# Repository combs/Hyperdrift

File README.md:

Hyperdrift is a panelized LED matrix artwork.

# LED panels
Each panel can have an arbitrary layout of LEDs, as long as they are electrically connected in a 4x16 matrix (4 common cathodes, 16 anodes).

## Mechanical specification

- [Spec PDF](https://github.com/combs/Hyperdrift/raw/refs/heads/main/Mechanical%20specs/Hyperdrift-Mechanical%20spec%20for%20LED%20panels.pdf) 

## Example LED panel layouts

### Grid
This is a straightforward grid of 8x8 pixels.
- [KiCad board and schematic](https://github.com/combs/Hyperdrift/tree/main/LED%20panel%20reference%20design%20-%20Grid)
- [BOM](https://github.com/combs/Hyperdrift/raw/refs/heads/main/LED%20panel%20reference%20design%20-%20Grid/bom/ibom.html) (download and open)
- [Schematic PDF](https://github.com/combs/Hyperdrift/raw/refs/heads/main/LED%20panel%20reference%20design%20-%20Grid/Hyperdrift-Grid.pdf) 
- [Board PDF](https://github.com/combs/Hyperdrift/raw/refs/heads/main/LED%20panel%20reference%20design%20-%20Grid/plots/Hyperdrift-Grid__Assembly.pdf) 

# Display controllers

Each display controller is a 75x100mm board that drives three LED panels (12x16 matrix arrangement). It accepts 12V in. It is designed to allow for either daisy-chained or wagon-wheel bus arrangement.

- [KiCad board and schematic](https://github.com/combs/Hyperdrift/tree/main/Display%20controller)
- [BOM](https://github.com/combs/Hyperdrift/raw/refs/heads/main/Display%20controller/bom/ibom.html) (download and open)
- [Schematic PDF](https://github.com/combs/Hyperdrift/raw/refs/heads/main/Display%20controller/Hyperdrift-Display-Controller.pdf) 
- [Board PDF](https://github.com/combs/Hyperdrift/raw/refs/heads/main/Display%20controller/Hyperdrift-Display-Controller-board.pdf)

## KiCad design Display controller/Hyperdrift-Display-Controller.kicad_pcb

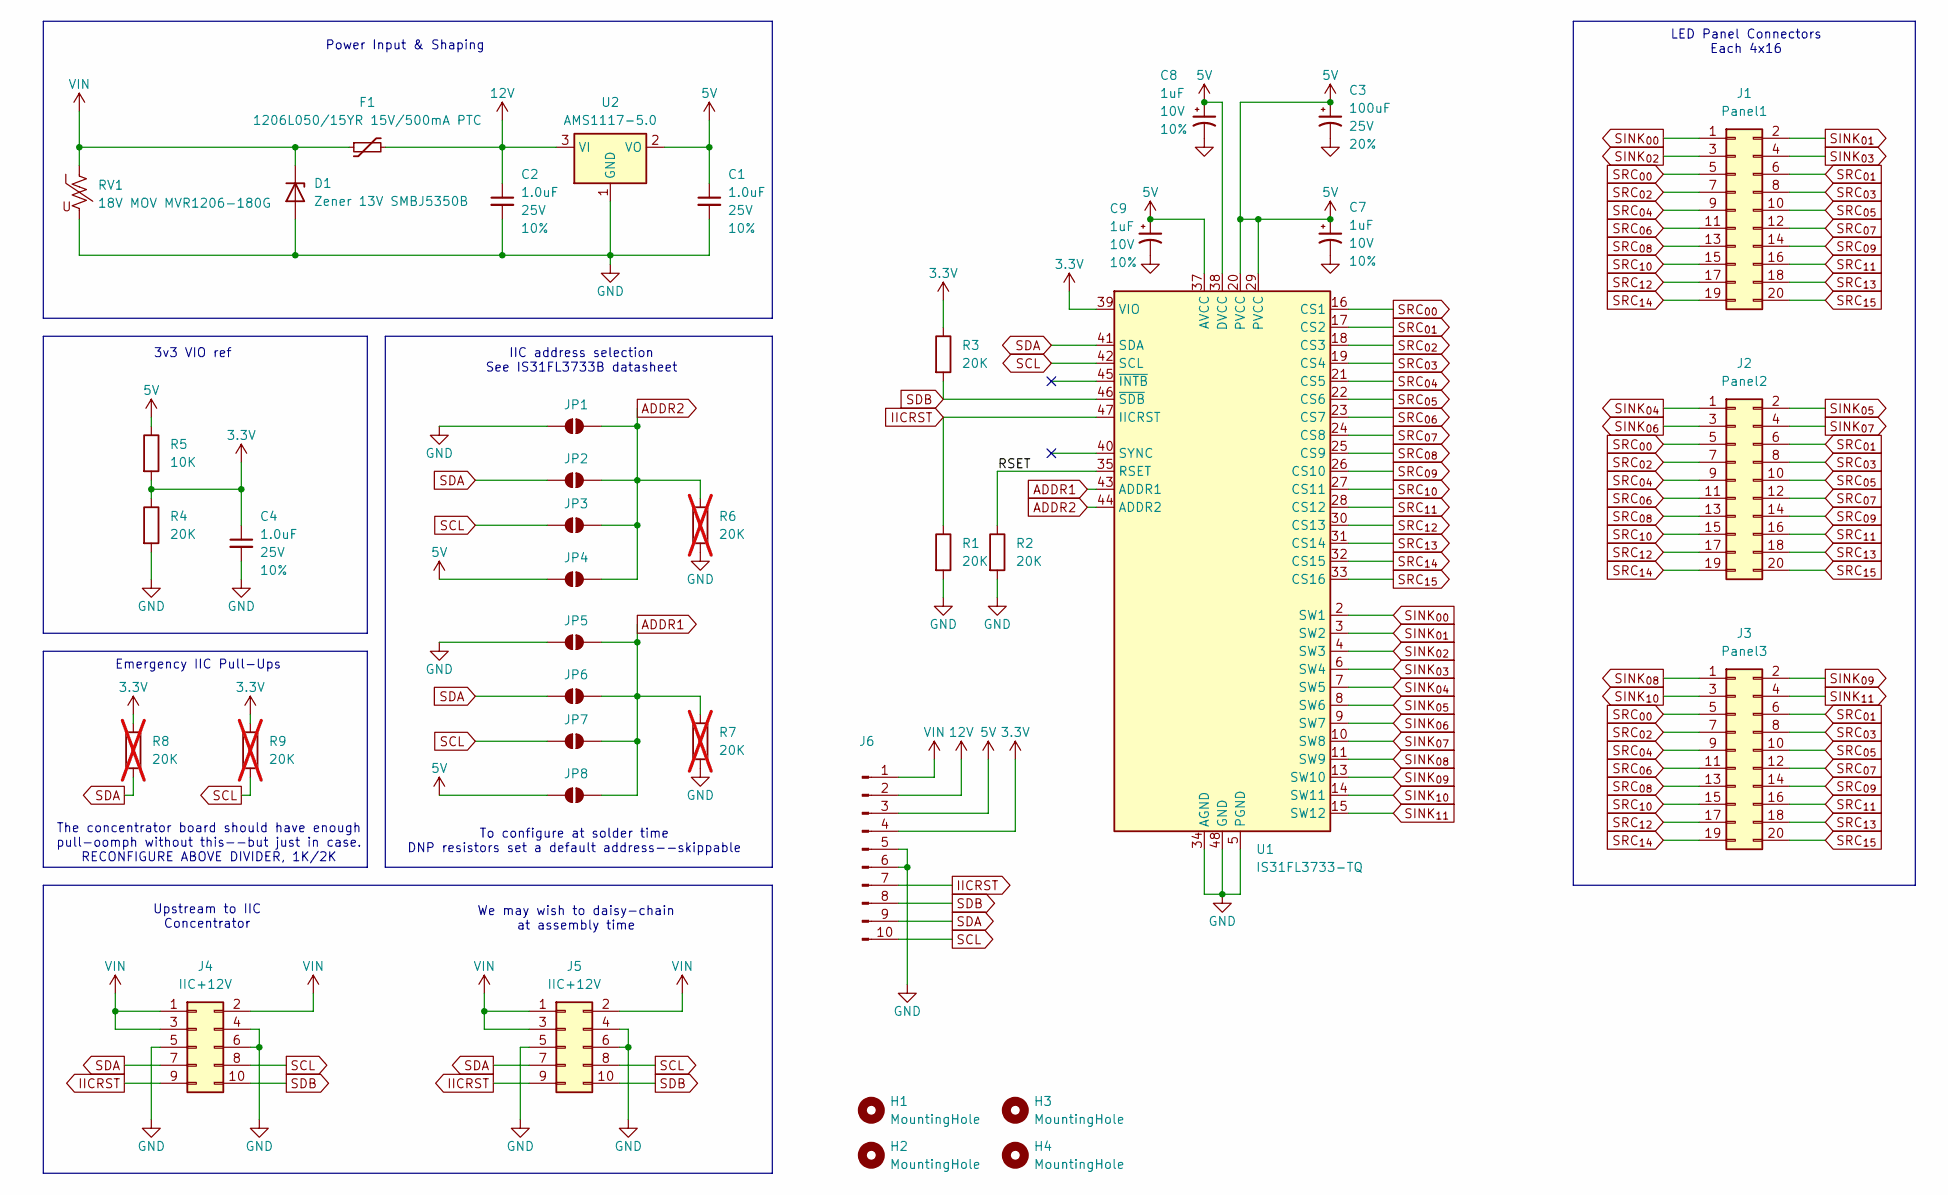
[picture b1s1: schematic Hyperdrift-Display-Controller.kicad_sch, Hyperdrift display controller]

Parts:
C1, C2, C4: 1.0uF; C_0805_2012Metric; Voltage 25V; Tolerance 10%
C3: 100uF; Panasonic_D; Voltage 25V; Tolerance 20%
C7, C8, C9: 1uF; CP_EIA-3216-10_Kemet-I_Pad1.58x1.35mm_HandSolder; Voltage 10V; Tolerance 10%
D1: Zener 13V SMBJ5350B; D_SMB
F1: 1206L050/15YR 15V/500mA PTC; 1206
H1, H2, H3, H4: MountingHole; MountingHole_3.2mm_M3
J1: Panel1; IDC-Header_2x10_P2.54mm_Vertical
J2: Panel2; IDC-Header_2x10_P2.54mm_Vertical
J3: Panel3; IDC-Header_2x10_P2.54mm_Vertical
J4, J5: IIC+12V; IDC-Header_2x05_P2.54mm_Vertical
J6: Conn_01x10_Pin; PinHeader_1x10_P2.54mm_Vertical
JP1: ADDR2 GND; SolderJumper-2_P1.3mm_Open_TrianglePad1.0x1.5mm
JP2: ADDR2 SDA; SolderJumper-2_P1.3mm_Open_TrianglePad1.0x1.5mm
JP3: ADDR2 SCL; SolderJumper-2_P1.3mm_Open_TrianglePad1.0x1.5mm
JP4: ADDR VCC; SolderJumper-2_P1.3mm_Open_TrianglePad1.0x1.5mm
JP5: ADDR1 GND; SolderJumper-2_P1.3mm_Open_TrianglePad1.0x1.5mm
JP6: ADDR1 SDA; SolderJumper-2_P1.3mm_Open_TrianglePad1.0x1.5mm
JP7: ADDR1 SCL; SolderJumper-2_P1.3mm_Open_TrianglePad1.0x1.5mm
JP8: ADDR1 VCC; SolderJumper-2_P1.3mm_Open_TrianglePad1.0x1.5mm
R1, R2, R3, R4: 20K; R_0805_2012Metric_Pad1.20x1.40mm_HandSolder
R5: 10K; R_0805_2012Metric_Pad1.20x1.40mm_HandSolder
R6, R7, R8, R9: 20K; R_0805_2012Metric_Pad1.20x1.40mm_HandSolder; not fitted
RV1: 18V MOV MVR1206-180G; R_1206_3216Metric_Pad1.30x1.75mm_HandSolder
U1: IS31FL3733-TQ; TQFP-48-1EP_7x7mm_P0.5mm_EP5x5mm
U2: AMS1117-5.0; SOT-223-3_TabPin2

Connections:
3.3V: C4.1, J6.4, R3.1, R4.1, R5.2, R8.1, R9.1, U1.39 (VIO)
5V: C1.1, C3.1, C7.1, C8.1, C9.1, J6.3, JP4.1 (A), JP8.1 (A), R5.1, U1.20 (PVCC), U1.29 (PVCC), U1.37 (AVCC), U1.38 (DVCC), U2.2 (VO)
12V: C2.1, F1.2, J6.2, U2.3 (VI)
/RSET: R2.1, U1.35 (RSET)
ADDR1: JP5.2 (B), JP6.2 (B), JP7.2 (B), JP8.2 (B), R7.1, U1.43 (ADDR1)
ADDR2: JP1.2 (B), JP2.2 (B), JP3.2 (B), JP4.2 (B), R6.1, U1.44 (ADDR2)
GND: C1.2, C2.2, C3.2, C4.2, C7.2, C8.2, C9.2, D1.2 (A), J4.4, J4.5, J4.6, J5.4, J5.5, J5.6, J6.5, J6.6, JP1.1 (A), JP5.1 (A), R1.2, R2.2, R4.2, R6.2, R7.2, RV1.2, U1.5 (PGND), U1.12 (PGND), U1.34 (AGND), U1.48 (GND), U1.49 (GND), U2.1 (GND)
IICRST: J4.9, J5.9, J6.7, R1.1, U1.47 (IICRST)
SCL: J4.8, J5.8, J6.10, JP3.1 (A), JP7.1 (A), R9.2, U1.42 (SCL)
SDA: J4.7, J5.7, J6.9, JP2.1 (A), JP6.1 (A), R8.2, U1.41 (SDA)
SDB: J4.10, J5.10, J6.8, R3.2, U1.46 (~SDB)
SINK_{00}: J1.1, U1.2 (SW1)
SINK_{01}: J1.2, U1.3 (SW2)
SINK_{02}: J1.3, U1.4 (SW3)
SINK_{03}: J1.4, U1.6 (SW4)
SINK_{04}: J2.1, U1.7 (SW5)
SINK_{05}: J2.2, U1.8 (SW6)
SINK_{06}: J2.3, U1.9 (SW7)
SINK_{07}: J2.4, U1.10 (SW8)
SINK_{08}: J3.1, U1.11 (SW9)
SINK_{09}: J3.2, U1.13 (SW10)
SINK_{10}: J3.3, U1.14 (SW11)
SINK_{11}: J3.4, U1.15 (SW12)
SRC_{00}: J1.5, J2.5, J3.5, U1.16 (CS1)
SRC_{01}: J1.6, J2.6, J3.6, U1.17 (CS2)
SRC_{02}: J1.7, J2.7, J3.7, U1.18 (CS3)
SRC_{03}: J1.8, J2.8, J3.8, U1.19 (CS4)
SRC_{04}: J1.9, J2.9, J3.9, U1.21 (CS5)
SRC_{05}: J1.10, J2.10, J3.10, U1.22 (CS6)
SRC_{06}: J1.11, J2.11, J3.11, U1.23 (CS7)
SRC_{07}: J1.12, J2.12, J3.12, U1.24 (CS8)
SRC_{08}: J1.13, J2.13, J3.13, U1.25 (CS9)
SRC_{09}: J1.14, J2.14, J3.14, U1.26 (CS10)
SRC_{10}: J1.15, J2.15, J3.15, U1.27 (CS11)
SRC_{11}: J1.16, J2.16, J3.16, U1.28 (CS12)
SRC_{12}: J1.17, J2.17, J3.17, U1.30 (CS13)
SRC_{13}: J1.18, J2.18, J3.18, U1.31 (CS14)
SRC_{14}: J1.19, J2.19, J3.19, U1.32 (CS15)
SRC_{15}: J1.20, J2.20, J3.20, U1.33 (CS16)
VIN: D1.1 (K), F1.1, J4.1, J4.2, J4.3, J5.1, J5.2, J5.3, J6.1, RV1.1

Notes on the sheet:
3v3 VIO ref
Emergency IIC Pull-Ups
To configure at solder time DNP resistors set a default address--skippable
Upstream to IIC Concentrator
IIC address selection See IS31FL3733B datasheet
The concentrator board should have enough pull-oomph without this--but just in case. RECONFIGURE ABOVE DIVIDER, 1K/2K
Power Input & Shaping
LED Panel Connectors Each 4x16
We may wish to daisy-chain at assembly time

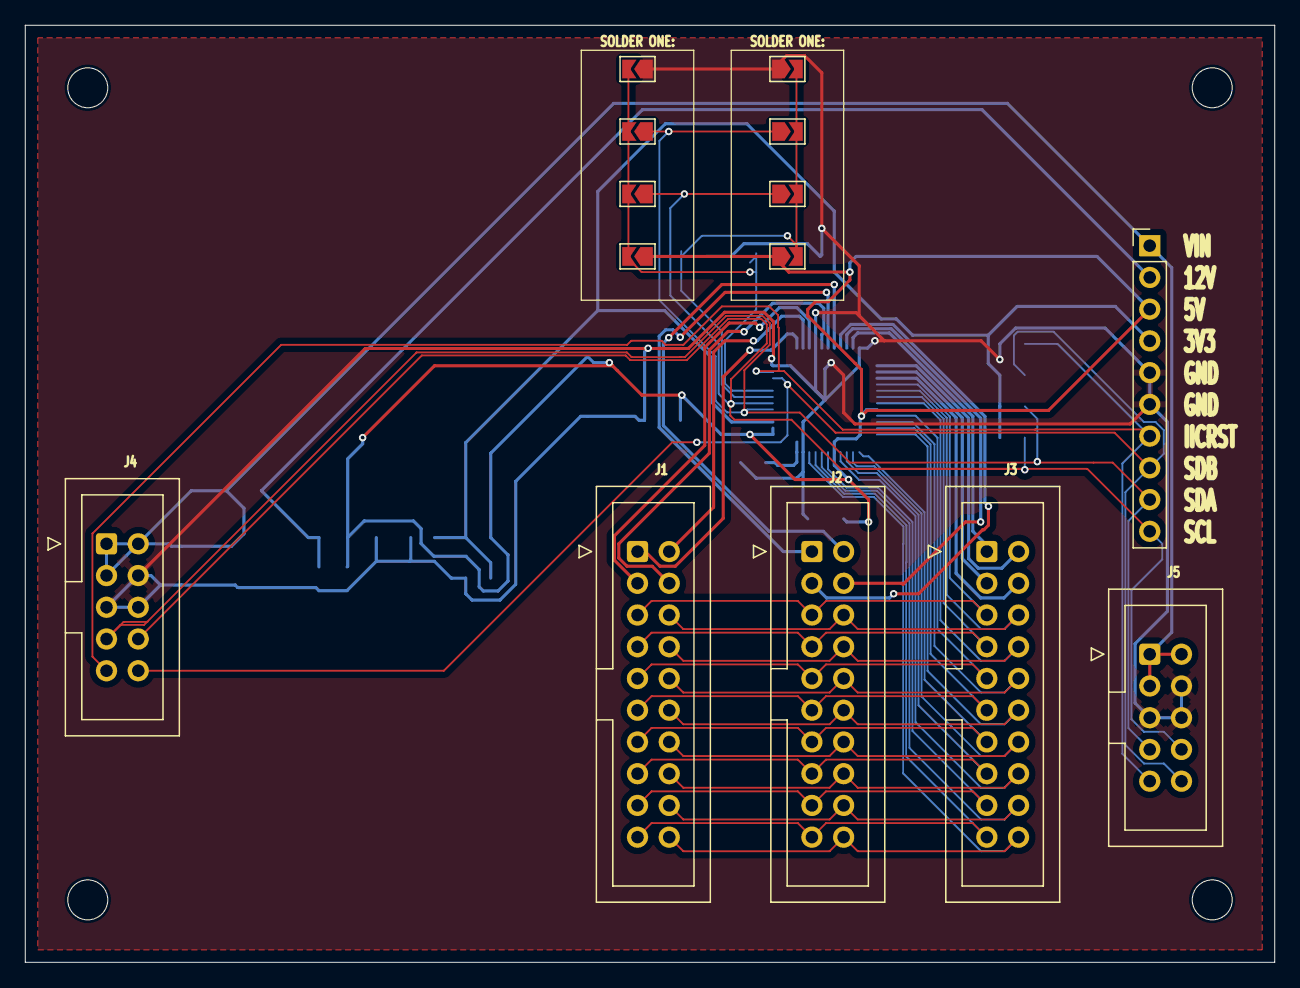
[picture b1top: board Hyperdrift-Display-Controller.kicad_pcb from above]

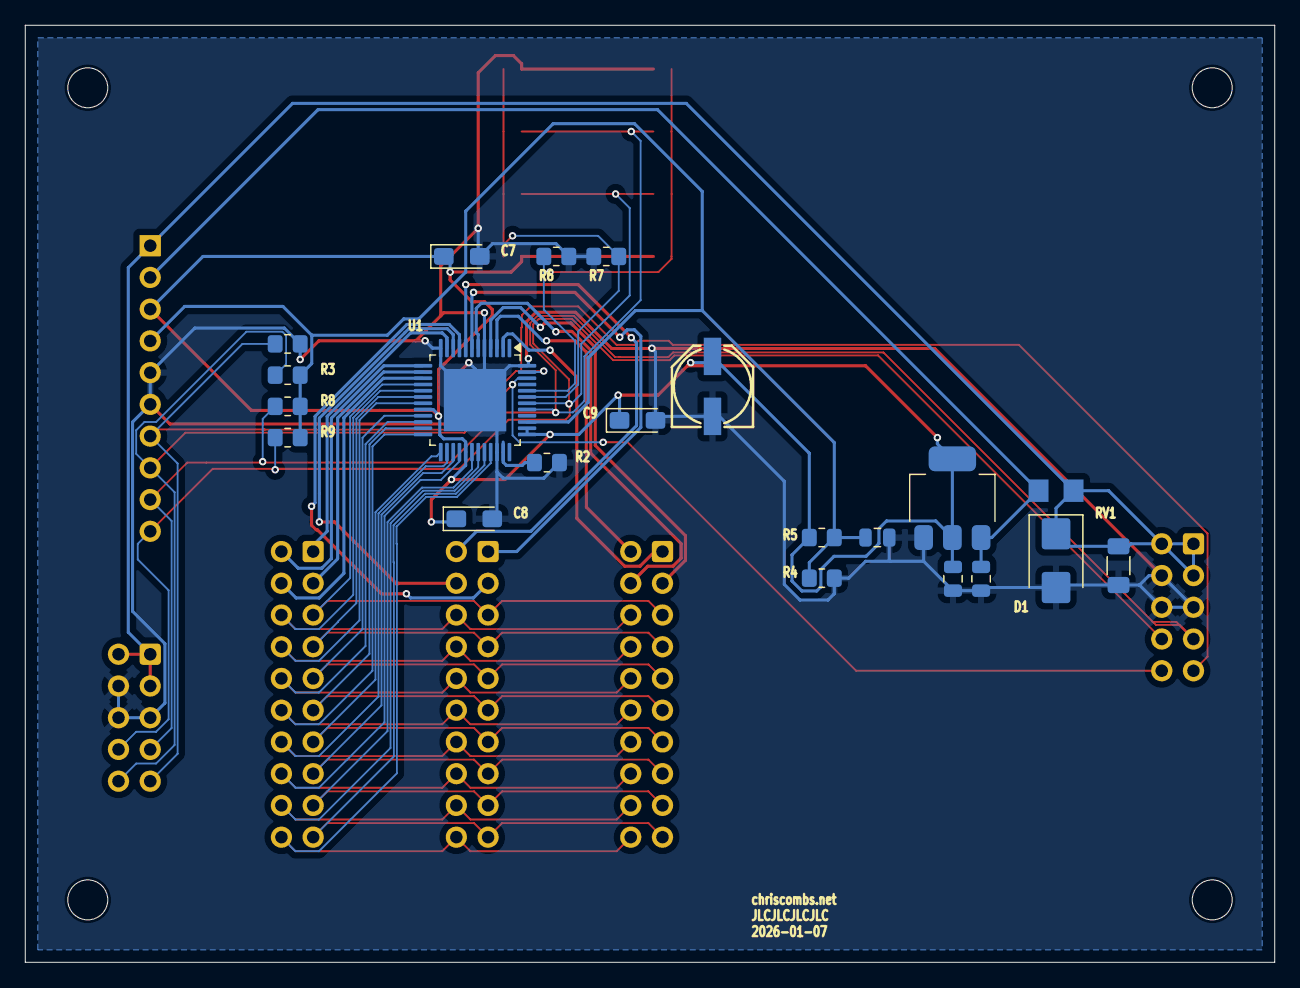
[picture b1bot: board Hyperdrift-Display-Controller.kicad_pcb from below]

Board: 2 copper layers, 100.0 x 75.0 mm, 39 parts (21 on the bottom side), 40 nets.

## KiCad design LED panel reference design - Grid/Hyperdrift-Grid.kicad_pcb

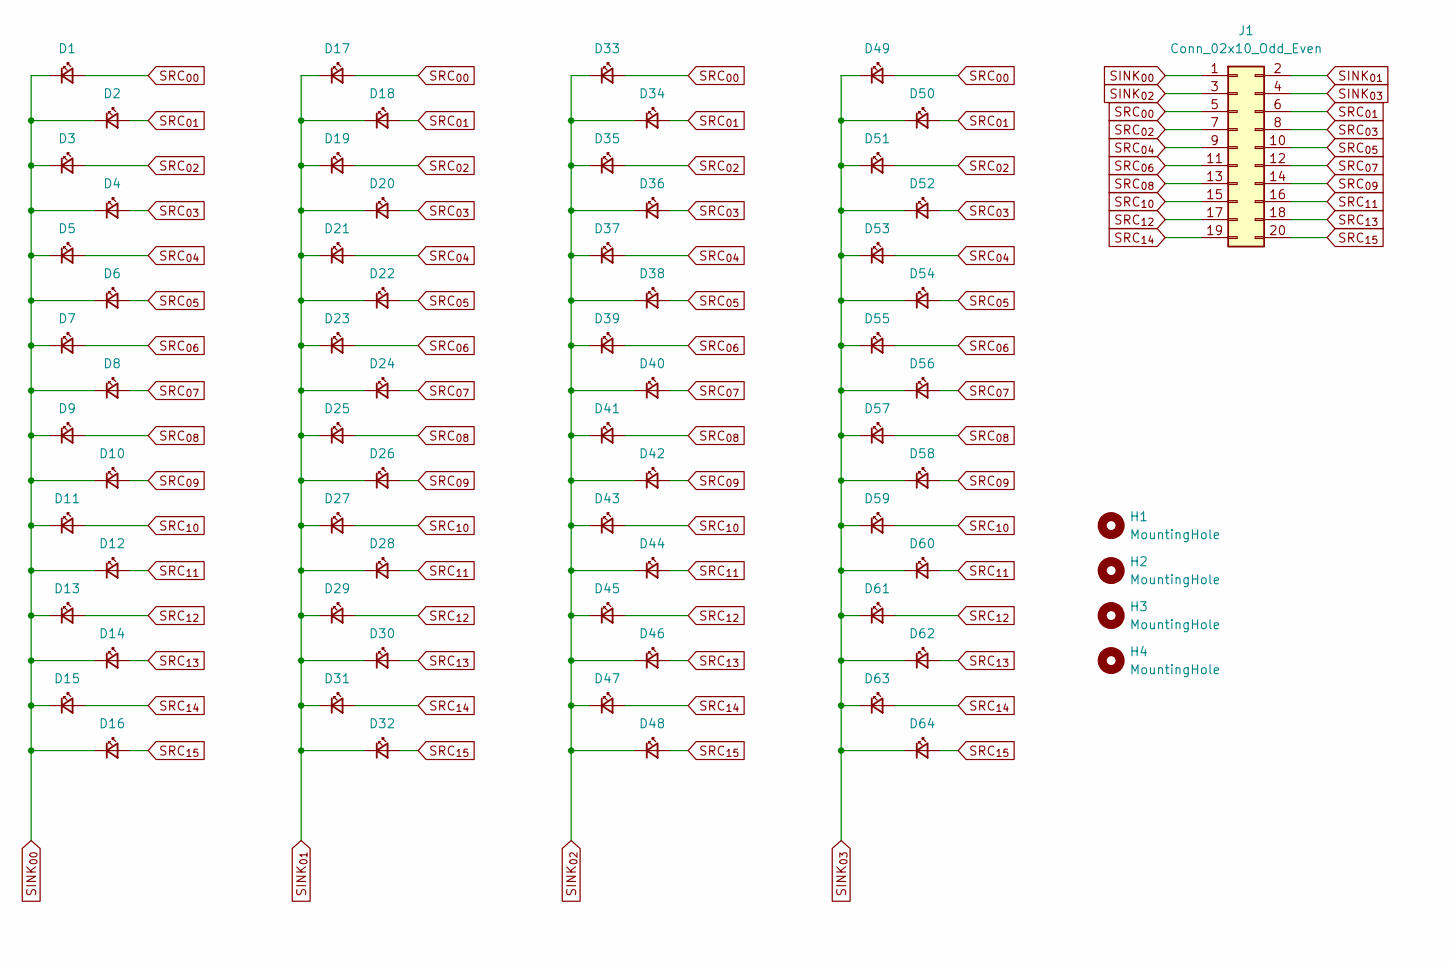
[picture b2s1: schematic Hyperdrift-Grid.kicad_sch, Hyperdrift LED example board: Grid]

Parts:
D1, D2, D3, D4, D5, D6, D7, D8, D9, D10, D11, D12, D13, D14, D15, D16, D17, D18, D19, D20, D21, D22, D23, D24, D25, D26, D27, D28, D29, D30, D31, D32, D33, D34, D35, D36, D37, D38, D39, D40, D41, D42, D43, D44, D45, D46, D47, D48, D49, D50, D51, D52, D53, D54, D55, D56, D57, D58, D59, D60, D61, D62, D63, D64: LED; LED_D5.0mm
H1, H2, H3, H4: MountingHole; MountingHole_3.2mm_M3
J1: Conn_02x10_Odd_Even; IDC-Header_2x10_P2.54mm_Vertical

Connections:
SINK_{00}: D1.1 (K), D2.1 (K), D3.1 (K), D4.1 (K), D5.1 (K), D6.1 (K), D7.1 (K), D8.1 (K), D9.1 (K), D10.1 (K), D11.1 (K), D12.1 (K), D13.1 (K), D14.1 (K), D15.1 (K), D16.1 (K), J1.1
SINK_{01}: D17.1 (K), D18.1 (K), D19.1 (K), D20.1 (K), D21.1 (K), D22.1 (K), D23.1 (K), D24.1 (K), D25.1 (K), D26.1 (K), D27.1 (K), D28.1 (K), D29.1 (K), D30.1 (K), D31.1 (K), D32.1 (K), J1.2
SINK_{02}: D33.1 (K), D34.1 (K), D35.1 (K), D36.1 (K), D37.1 (K), D38.1 (K), D39.1 (K), D40.1 (K), D41.1 (K), D42.1 (K), D43.1 (K), D44.1 (K), D45.1 (K), D46.1 (K), D47.1 (K), D48.1 (K), J1.3
SINK_{03}: D49.1 (K), D50.1 (K), D51.1 (K), D52.1 (K), D53.1 (K), D54.1 (K), D55.1 (K), D56.1 (K), D57.1 (K), D58.1 (K), D59.1 (K), D60.1 (K), D61.1 (K), D62.1 (K), D63.1 (K), D64.1 (K), J1.4
SRC_{00}: D1.2 (A), D17.2 (A), D33.2 (A), D49.2 (A), J1.5
SRC_{01}: D2.2 (A), D18.2 (A), D34.2 (A), D50.2 (A), J1.6
SRC_{02}: D3.2 (A), D19.2 (A), D35.2 (A), D51.2 (A), J1.7
SRC_{03}: D4.2 (A), D20.2 (A), D36.2 (A), D52.2 (A), J1.8
SRC_{04}: D5.2 (A), D21.2 (A), D37.2 (A), D53.2 (A), J1.9
SRC_{05}: D6.2 (A), D22.2 (A), D38.2 (A), D54.2 (A), J1.10
SRC_{06}: D7.2 (A), D23.2 (A), D39.2 (A), D55.2 (A), J1.11
SRC_{07}: D8.2 (A), D24.2 (A), D40.2 (A), D56.2 (A), J1.12
SRC_{08}: D9.2 (A), D25.2 (A), D41.2 (A), D57.2 (A), J1.13
SRC_{09}: D10.2 (A), D26.2 (A), D42.2 (A), D58.2 (A), J1.14
SRC_{10}: D11.2 (A), D27.2 (A), D43.2 (A), D59.2 (A), J1.15
SRC_{11}: D12.2 (A), D28.2 (A), D44.2 (A), D60.2 (A), J1.16
SRC_{12}: D13.2 (A), D29.2 (A), D45.2 (A), D61.2 (A), J1.17
SRC_{13}: D14.2 (A), D30.2 (A), D46.2 (A), D62.2 (A), J1.18
SRC_{14}: D15.2 (A), D31.2 (A), D47.2 (A), D63.2 (A), J1.19
SRC_{15}: D16.2 (A), D32.2 (A), D48.2 (A), D64.2 (A), J1.20

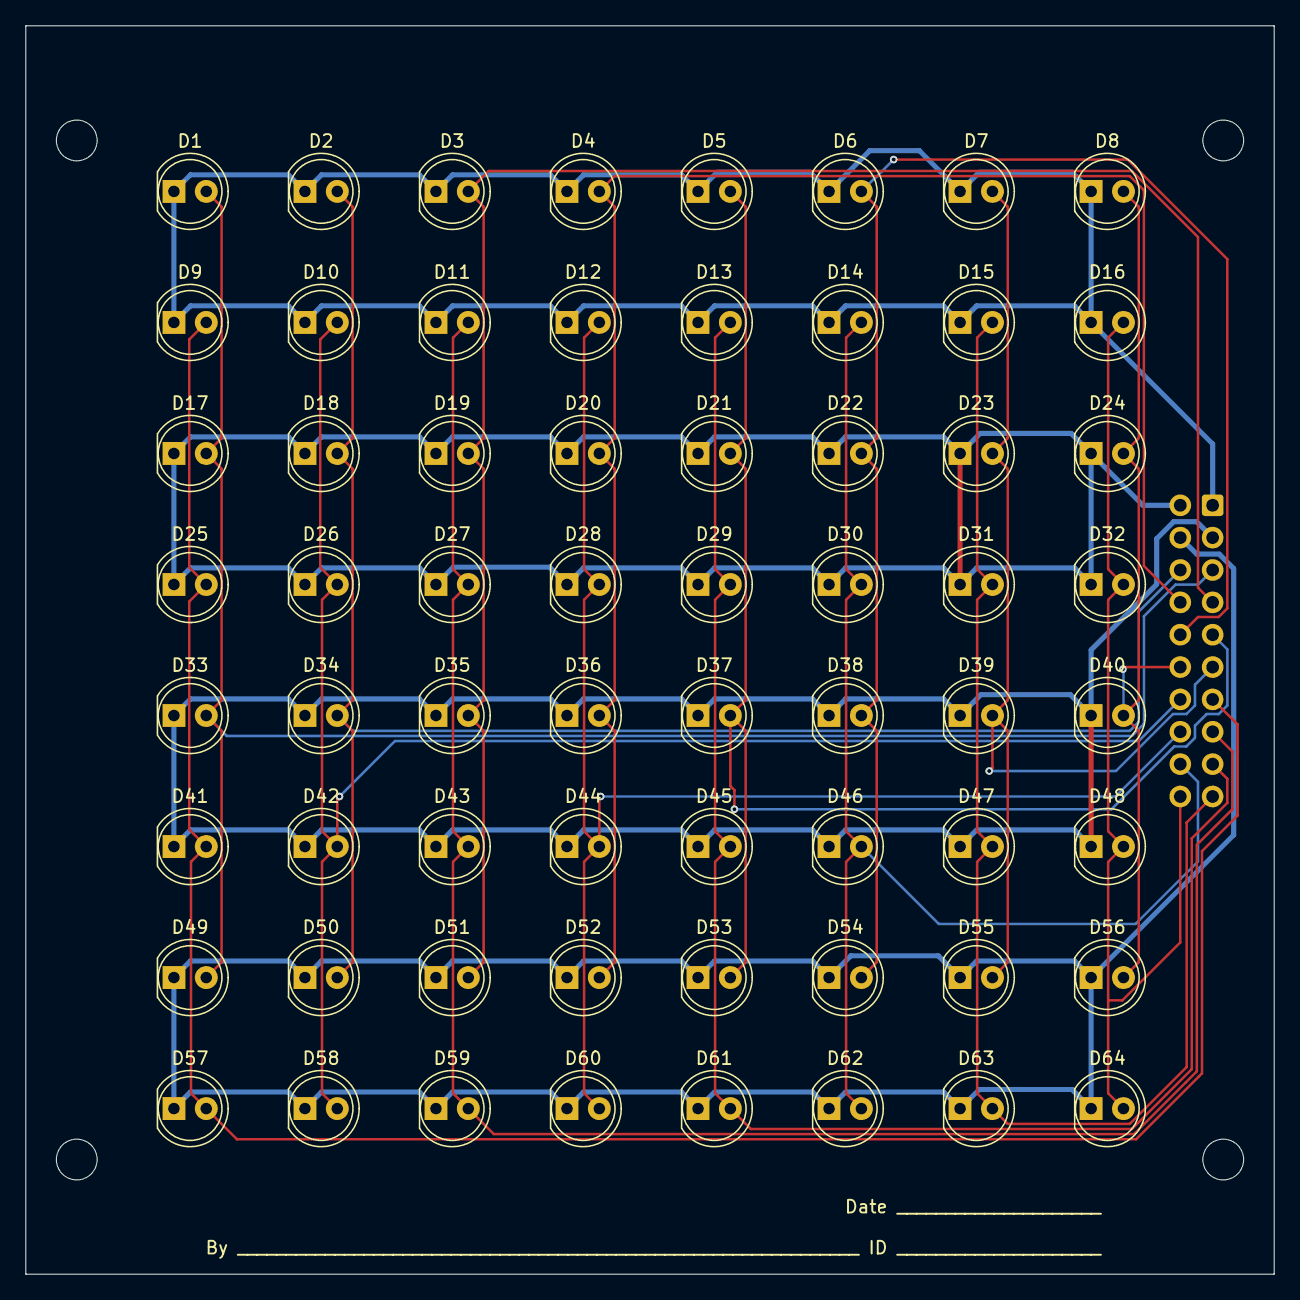
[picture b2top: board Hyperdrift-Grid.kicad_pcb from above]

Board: 2 copper layers, 98.0 x 98.0 mm, 69 parts (1 on the bottom side), 20 nets.

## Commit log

2026-01-06 Initial working version
2026-01-06 Update ibom
2026-01-07 Add Hyperdrift-Display-Controller
2026-01-07 Add ground pour for Hyperdrift-Display-Controller
2026-01-07 A barebones readme
2026-01-07 Fix formatting
